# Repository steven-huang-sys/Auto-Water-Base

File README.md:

# Senior Design Project Fall 2024
## Autonomous Watering System - Base Station
This repository contains the code for the microcontroller used in the base station of the system. Not everything is uploaded as the repository would be way too big with the build files. I used the ESP-IDF setup within VSCode.

## Specifications
### Microcontrollers
Tested on an ESP-WROOM-32
Intended to be an ESP32-S3 on the final product

### Display
2.2in TFT LCD Display with ILI9488 Drivers. SPI interface

## Schematic Notes
This is on KiCAD 6.0. Footprints for the ESP32 can be found here: https://github.com/espressif/kicad-libraries/tree/legacy_kicad6?tab=readme-ov-file

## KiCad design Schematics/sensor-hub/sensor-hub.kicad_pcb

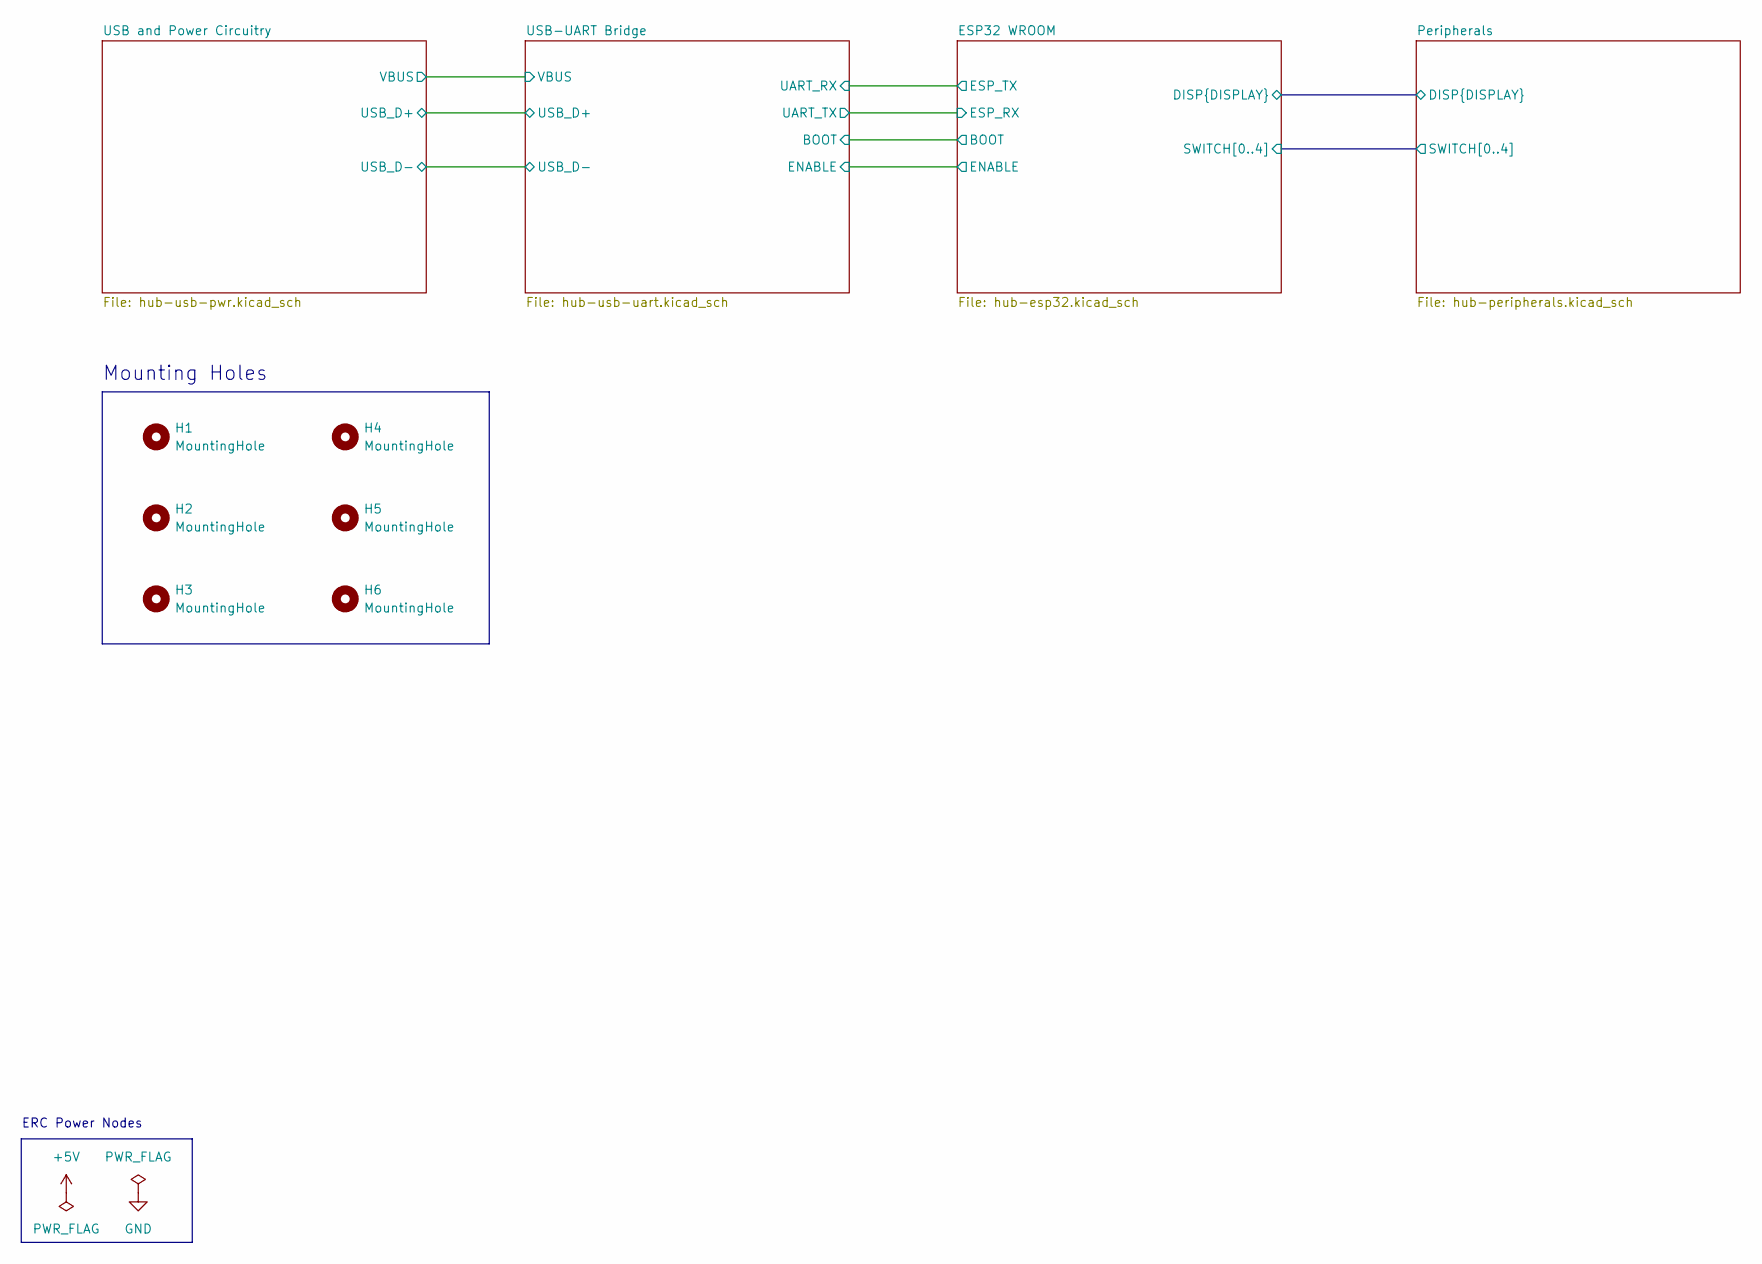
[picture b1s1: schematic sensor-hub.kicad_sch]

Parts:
H1, H2, H3, H4, H5, H6: MountingHole; MountingHole_3.2mm_M3

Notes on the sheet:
ERC Power Nodes
Mounting Holes

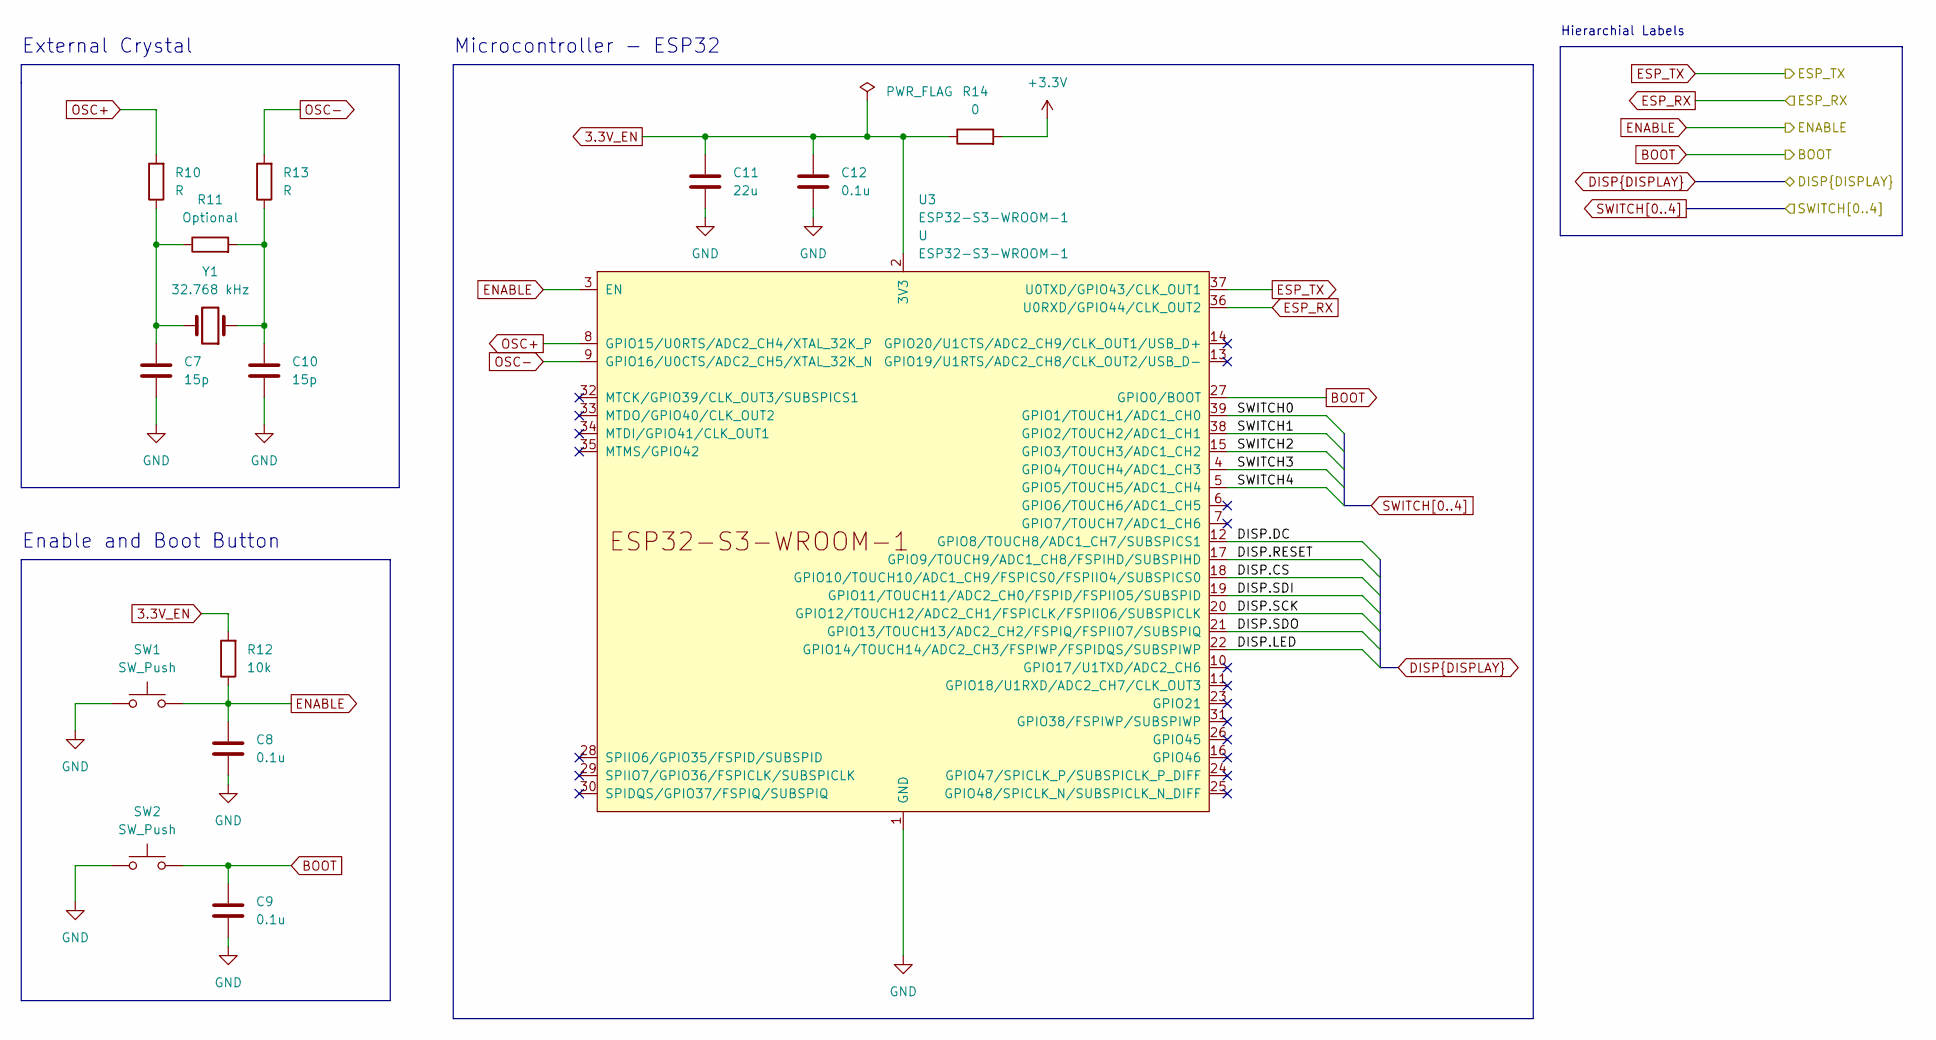
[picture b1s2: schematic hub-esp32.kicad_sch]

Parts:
C7, C10: 15p; C_0805_2012Metric_Pad1.18x1.45mm_HandSolder
C8, C9, C12: 0.1u; C_0805_2012Metric_Pad1.18x1.45mm_HandSolder
C11: 22u; C_0805_2012Metric_Pad1.18x1.45mm_HandSolder
R10, R13: R; R_0805_2012Metric_Pad1.20x1.40mm_HandSolder
R11: Optional; R_0805_2012Metric_Pad1.20x1.40mm_HandSolder
R12: 10k; R_0805_2012Metric_Pad1.20x1.40mm_HandSolder
R14: 0; R_0805_2012Metric_Pad1.20x1.40mm_HandSolder
SW1, SW2: SW_Push; Switch_Small
U3: ESP32-S3-WROOM-1; ESP32-S3-WROOM-1U
Y1: 32.768 kHz; Crystal_SMD_3215-2Pin_3.2x1.5mm

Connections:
3.3V_EN: C11.2, C12.2, R12.2, R14.1, U3.2 (3V3)
+3V3: R14.2; also elsewhere on the board
BOOT: C9.2, SW2.2, U3.27 (GPIO0/BOOT); also elsewhere on the board
DISP.CS: U3.18 (GPIO10/TOUCH10/ADC1_CH9/FSPICS0/FSPIIO4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); also elsewhere on the board
DISP.DC: U3.12 (GPIO8/TOUCH8/ADC1_CH7/SUBSPICS1); also elsewhere on the board
DISP.LED: U3.22 (GPIO14/TOUCH14/ADC2_CH3/FSPIWP/FSPIDQS/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); also elsewhere on the board
DISP.RESET: U3.17 (GPIO9/TOUCH9/ADC1_CH8/FSPIHD/SUBSPIHD); also elsewhere on the board
DISP.SCK: U3.20 (GPIO12/TOUCH12/ADC2_CH1/FSPICLK/FSPIIO6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); also elsewhere on the board
DISP.SDI: U3.19 (GPIO11/TOUCH11/ADC2_CH0/FSPID/FSPIIO5/S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); also elsewhere on the board
DISP.SDO: U3.21 (GPIO13/TOUCH13/ADC2_CH2/FSPIQ/FSPIIO7/S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); also elsewhere on the board
ENABLE: C8.2, R12.1, SW1.2, U3.3 (EN); also elsewhere on the board
ESP_RX: U3.36 (U0RXD/GPIO44/CLK_OUT2); also elsewhere on the board
GND: C7.2, C8.1, C9.1, C10.2, C11.1, C12.1, SW1.1, SW2.1, U3.1 (GND), U3.40 (GND), U3.41 (GND); also elsewhere on the board
unnamed: C7.1, R10.1, R11.1, Y1.2
unnamed: C10.1, R11.2, R13.1, Y1.1
OSC+: R10.2, U3.8 (GPIO15/U0RTS/ADC2_CH4/XTAL_32K_P)
OSC-: R13.2, U3.9 (GPIO16/U0CTS/ADC2_CH5/XTAL_32K_N)
SWITCH0: U3.39 (GPIO1/TOUCH1/ADC1_CH0); also elsewhere on the board
SWITCH1: U3.38 (GPIO2/TOUCH2/ADC1_CH1); also elsewhere on the board
SWITCH2: U3.15 (GPIO3/TOUCH3/ADC1_CH2); also elsewhere on the board
SWITCH3: U3.4 (GPIO4/TOUCH4/ADC1_CH3); also elsewhere on the board
SWITCH4: U3.5 (GPIO5/TOUCH5/ADC1_CH4); also elsewhere on the board
UART_RX: U3.37 (U0TXD/GPIO43/CLK_OUT1); also elsewhere on the board

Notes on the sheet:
External Crystal
Enable and Boot Button
Hierarchial Labels
Microcontroller - ESP32

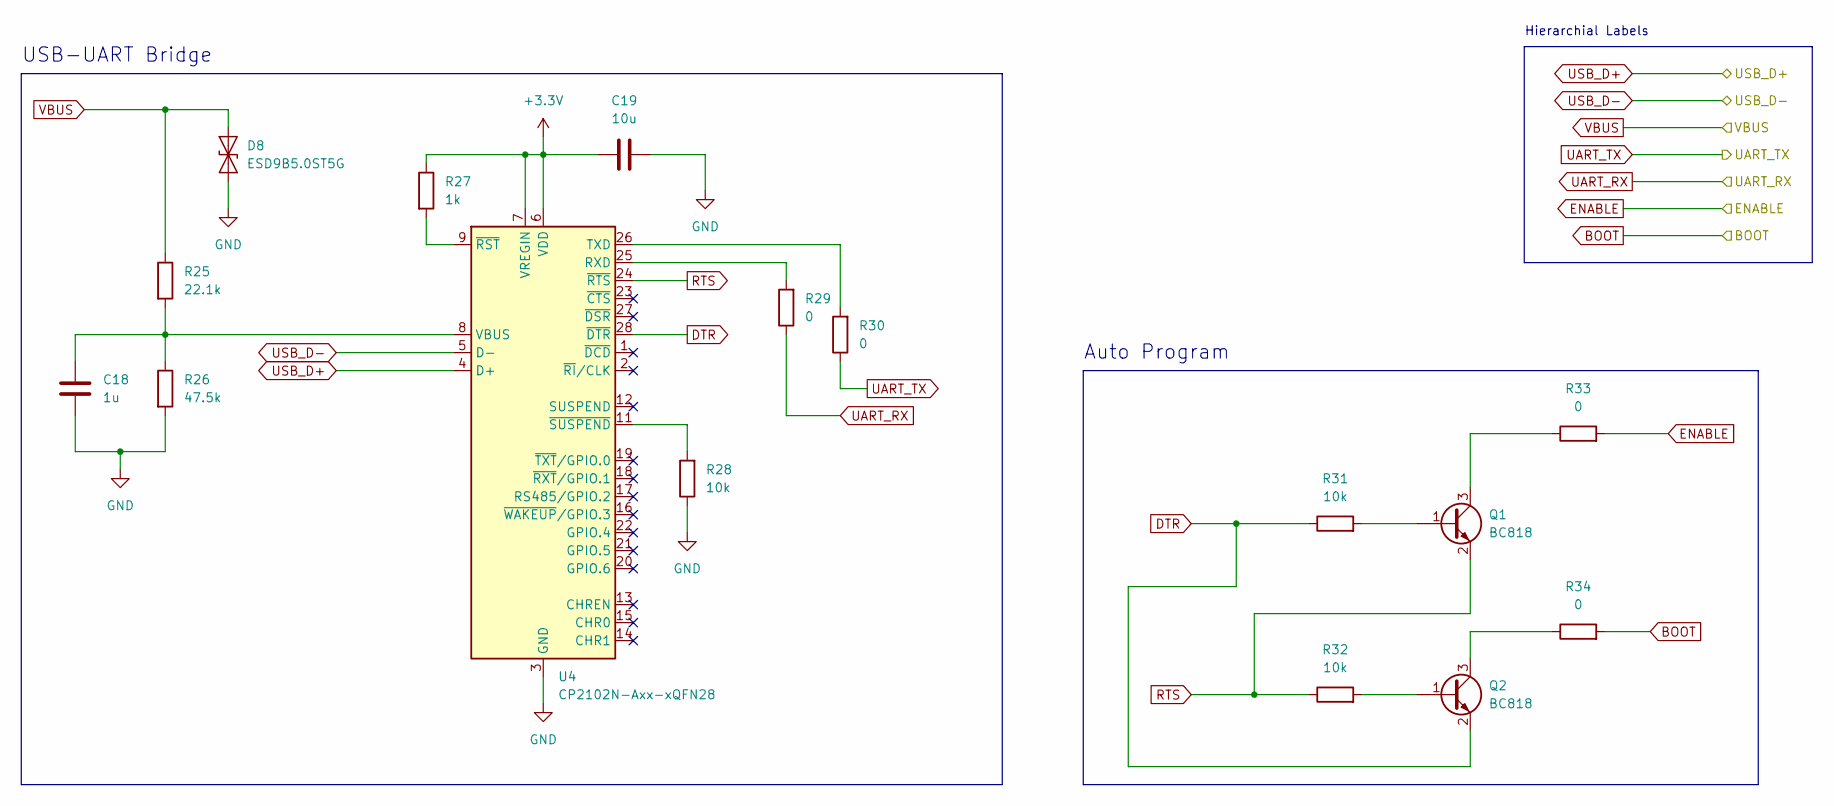
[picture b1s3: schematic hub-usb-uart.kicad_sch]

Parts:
C18: 1u; C_0805_2012Metric_Pad1.18x1.45mm_HandSolder
C19: 10u; C_0805_2012Metric_Pad1.18x1.45mm_HandSolder
D8: ESD9B5.0ST5G; D_SOD-923
Q1, Q2: BC818; SOT-23
R25: 22.1k; R_0805_2012Metric_Pad1.20x1.40mm_HandSolder
R26: 47.5k; R_0805_2012Metric_Pad1.20x1.40mm_HandSolder
R27: 1k; R_0805_2012Metric_Pad1.20x1.40mm_HandSolder
R28, R31, R32: 10k; R_0805_2012Metric_Pad1.20x1.40mm_HandSolder
R29, R30, R33, R34: 0; R_0805_2012Metric_Pad1.20x1.40mm_HandSolder
U4: CP2102N-Axx-xQFN28; QFN-28-1EP_5x5mm_P0.5mm_EP3.35x3.35mm

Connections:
+3V3: C19.1, R27.1, U4.6 (VDD), U4.7 (VREGIN); also elsewhere on the board
BOOT: R34.2; also elsewhere on the board
DTR: Q2.2 (E), R31.1, U4.28 (~DTR)
ENABLE: R33.2; also elsewhere on the board
ESP_RX: R30.1; also elsewhere on the board
GND: C18.1, C19.2, D8.2 (A2), R26.2, R28.1, U4.3 (GND), U4.29 (GND); also elsewhere on the board
unnamed: C18.2, R25.2, R26.1, U4.8 (VBUS)
unnamed: Q1.1 (B), R31.2
unnamed: Q1.3 (C), R33.1
unnamed: Q2.1 (B), R32.2
unnamed: Q2.3 (C), R34.1
unnamed: R27.2, U4.9 (~RST)
unnamed: R28.2, U4.11 (~SUSPEND)
unnamed: R29.2, U4.25 (RXD)
unnamed: R30.2, U4.26 (TXD)
RTS: Q1.2 (E), R32.1, U4.24 (~RTS)
UART_RX: R29.1; also elsewhere on the board
USB_D+: U4.4 (D+); also elsewhere on the board
USB_D-: U4.5 (D-); also elsewhere on the board
VBUS: D8.1 (A1), R25.1; also elsewhere on the board

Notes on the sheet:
Auto Program
Hierarchial Labels
USB-UART Bridge

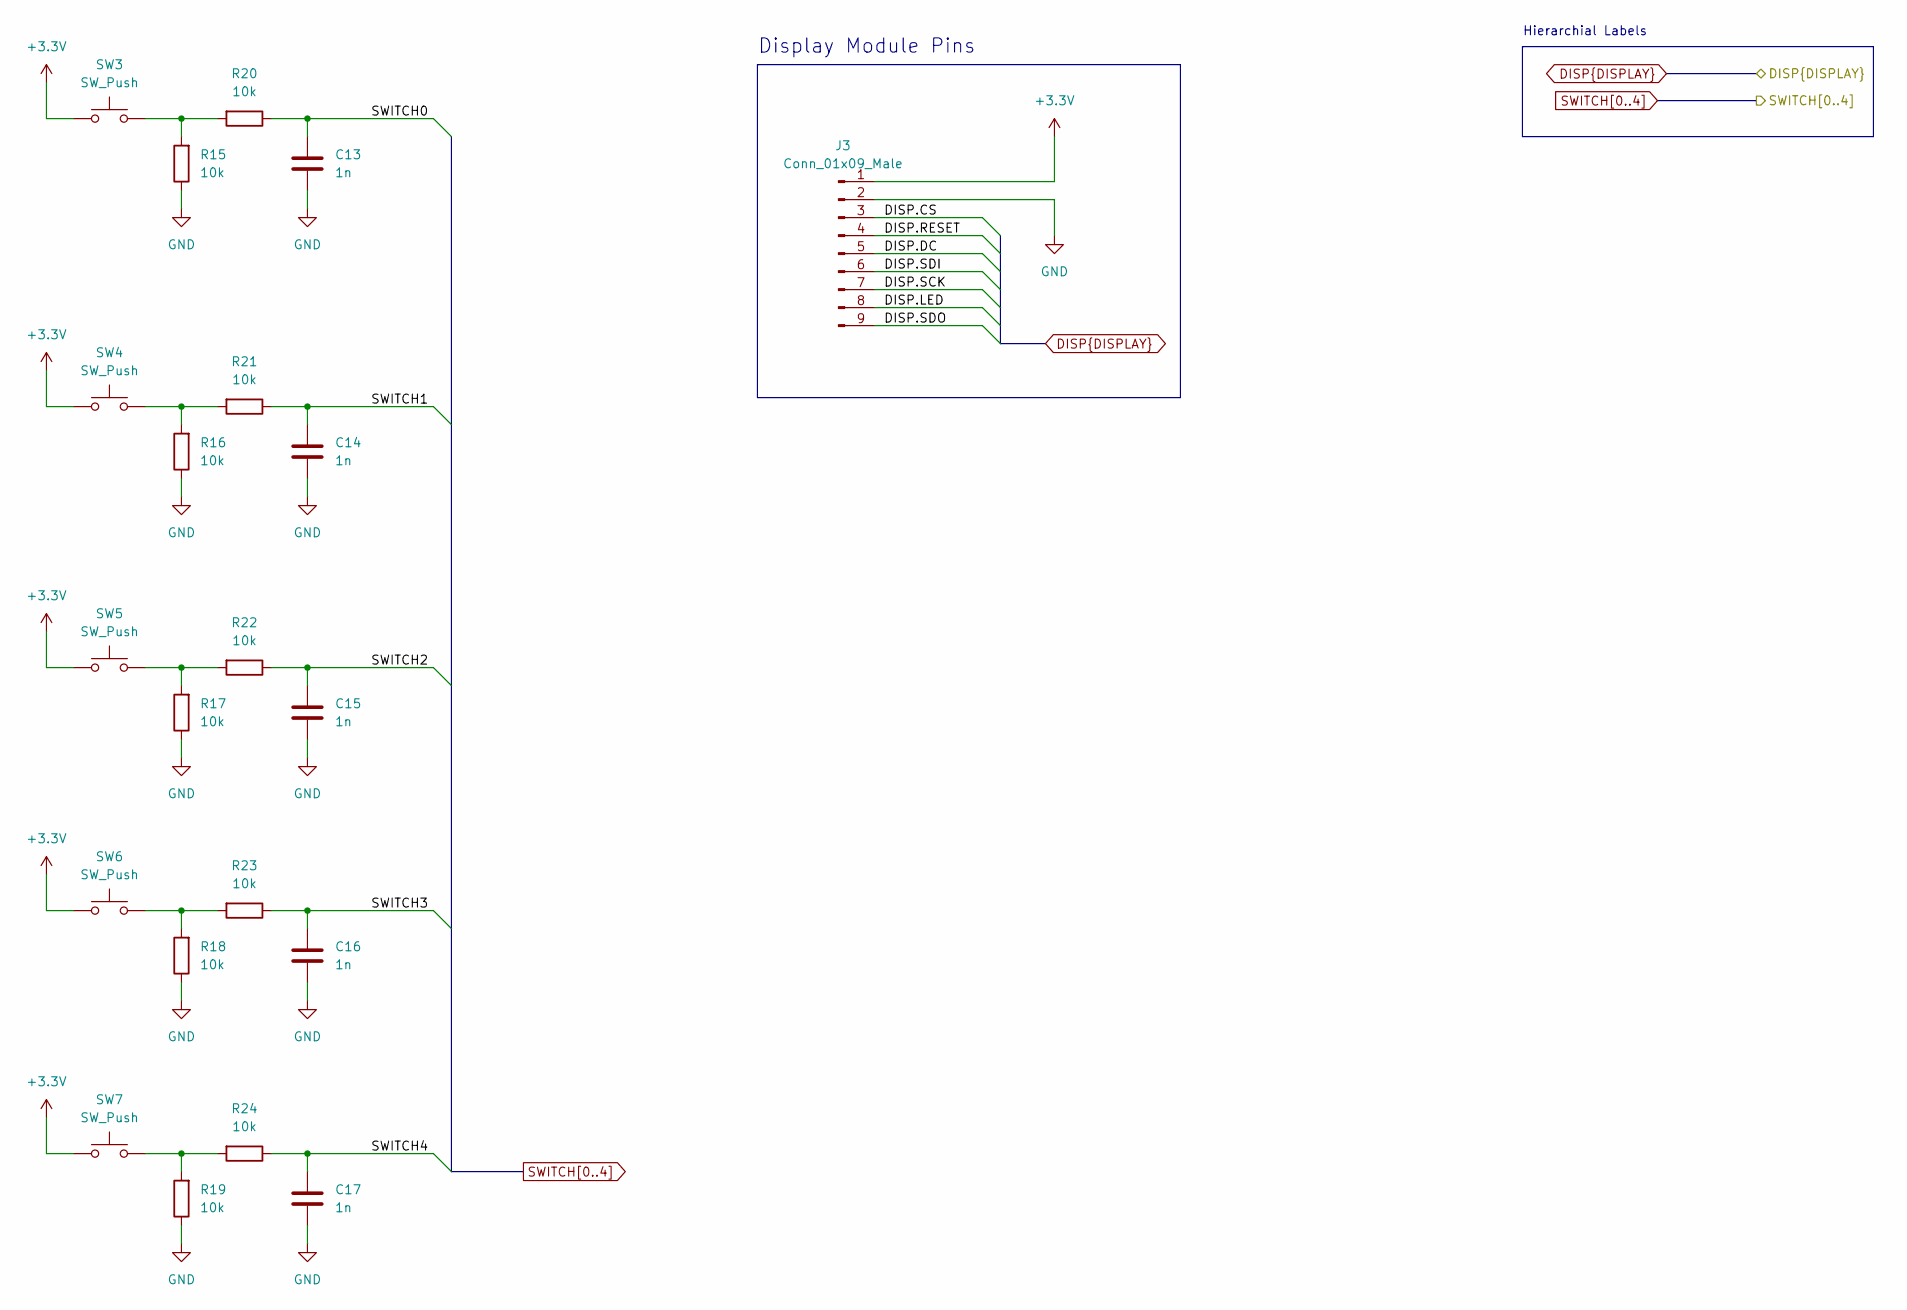
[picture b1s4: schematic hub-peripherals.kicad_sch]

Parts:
C13, C14, C15, C16, C17: 1n; C_0805_2012Metric_Pad1.18x1.45mm_HandSolder
J3: Conn_01x09_Male; PinHeader_1x09_P2.54mm_Vertical
R15, R16, R17, R18, R19, R20, R21, R22, R23, R24: 10k; R_0805_2012Metric_Pad1.20x1.40mm_HandSolder
SW3, SW4, SW5, SW6, SW7: SW_Push; SW_PUSH-12mm

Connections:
+3V3: J3.1, SW3.1, SW4.1, SW5.1, SW6.1, SW7.1; also elsewhere on the board
DISP.CS: J3.3; also elsewhere on the board
DISP.DC: J3.5; also elsewhere on the board
DISP.LED: J3.8; also elsewhere on the board
DISP.RESET: J3.4; also elsewhere on the board
DISP.SCK: J3.7; also elsewhere on the board
DISP.SDI: J3.6; also elsewhere on the board
DISP.SDO: J3.9; also elsewhere on the board
GND: C13.1, C14.1, C15.1, C16.1, C17.1, J3.2, R15.1, R16.1, R17.1, R18.1, R19.1; also elsewhere on the board
unnamed: R15.2, R20.2, SW3.2
unnamed: R16.2, R21.2, SW4.2
unnamed: R17.2, R22.2, SW5.2
unnamed: R18.2, R23.2, SW6.2
unnamed: R19.2, R24.2, SW7.2
SWITCH0: C13.2, R20.1; also elsewhere on the board
SWITCH1: C14.2, R21.1; also elsewhere on the board
SWITCH2: C15.2, R22.1; also elsewhere on the board
SWITCH3: C16.2, R23.1; also elsewhere on the board
SWITCH4: C17.2, R24.1; also elsewhere on the board

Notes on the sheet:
Display Module Pins
Hierarchial Labels

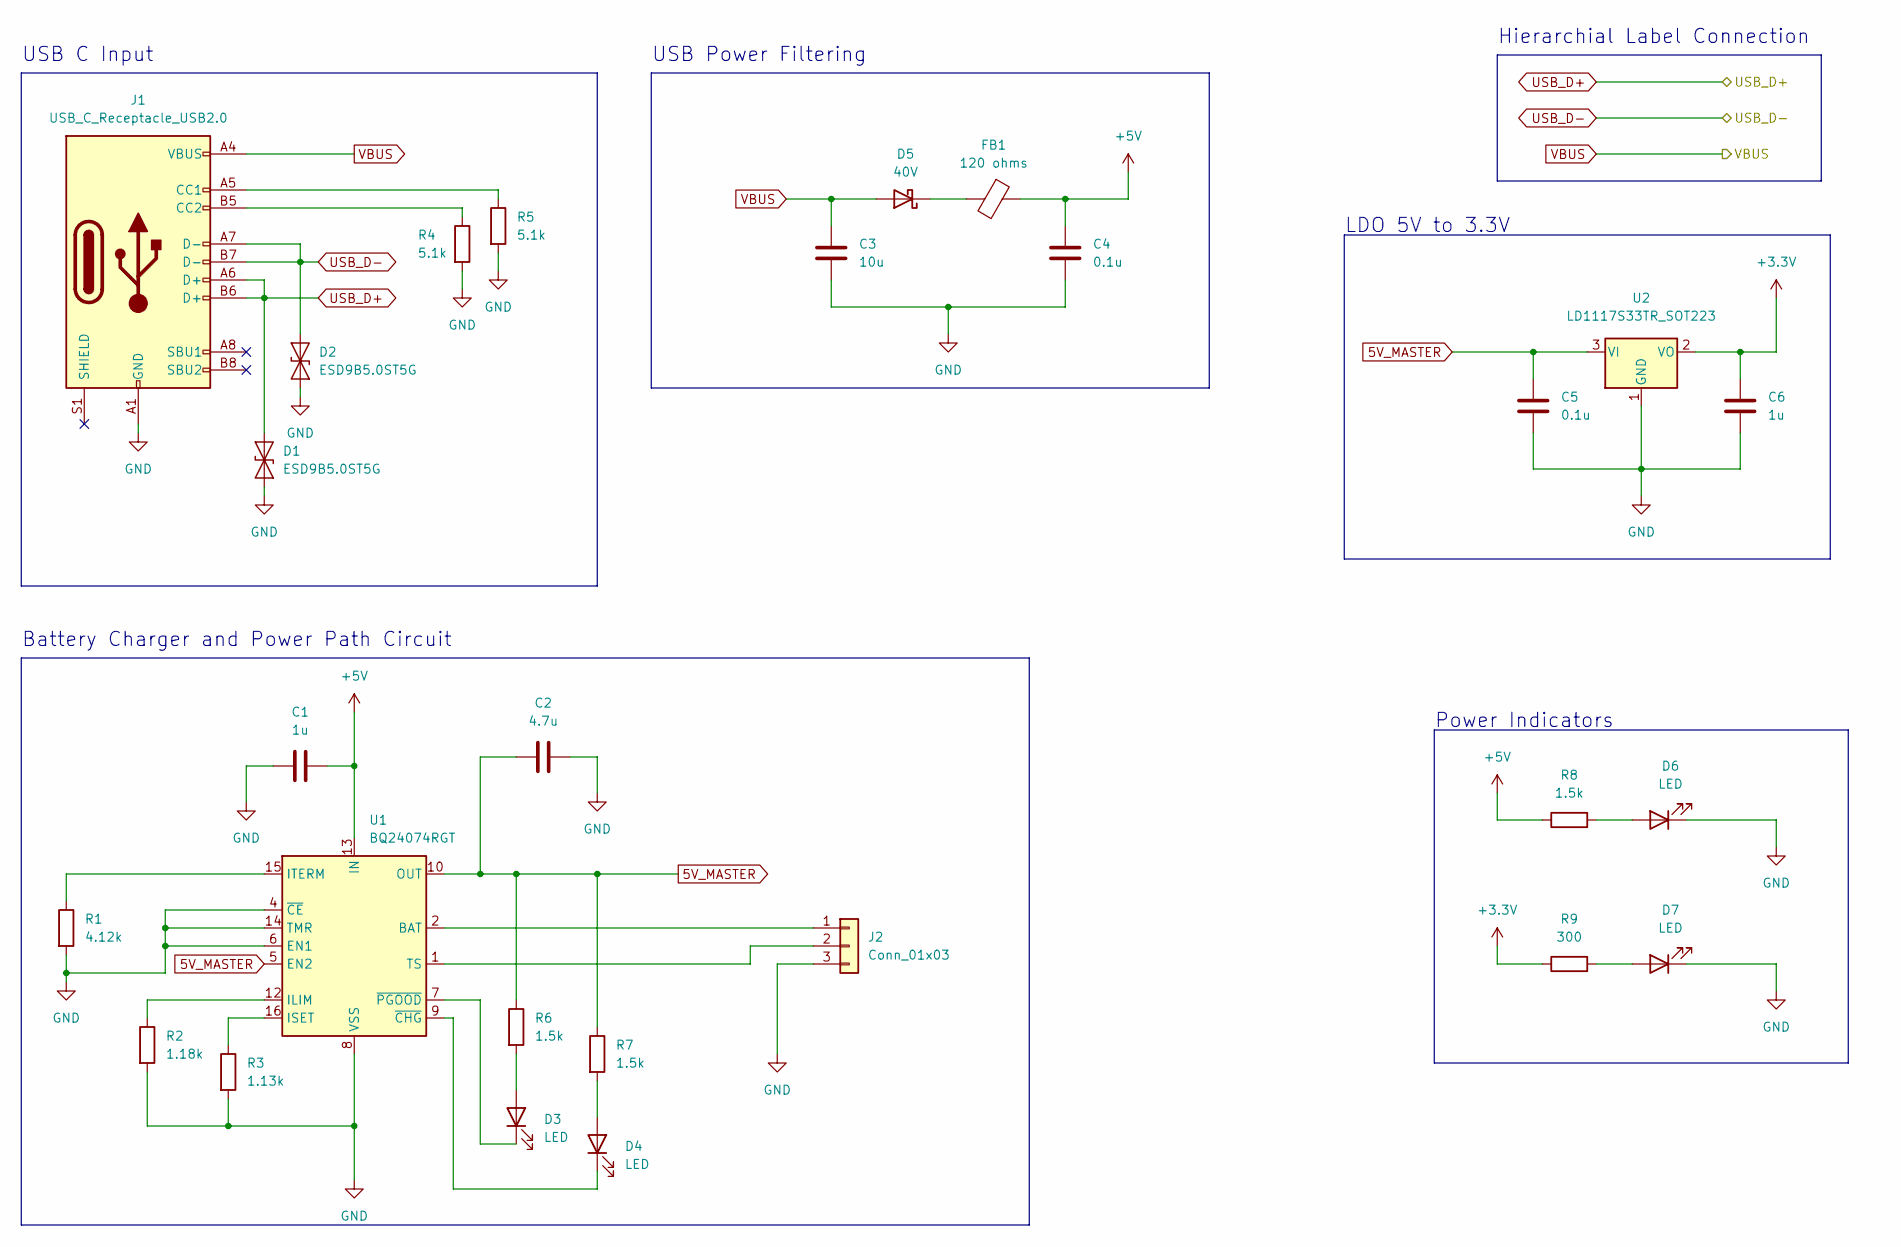
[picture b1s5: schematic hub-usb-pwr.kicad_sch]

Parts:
C1, C6: 1u; C_0805_2012Metric_Pad1.18x1.45mm_HandSolder
C2: 4.7u; C_0805_2012Metric_Pad1.18x1.45mm_HandSolder
C3: 10u; C_0805_2012Metric_Pad1.18x1.45mm_HandSolder
C4, C5: 0.1u; C_0805_2012Metric_Pad1.18x1.45mm_HandSolder
D1, D2: ESD9B5.0ST5G; D_SOD-923
D3, D4, D6, D7: LED; LED_0805_2012Metric_Pad1.15x1.40mm_HandSolder
D5: 40V; D_SOD-123F
FB1: 120 ohms; R_0805_2012Metric_Pad1.20x1.40mm_HandSolder
J1: USB_C_Receptacle_USB2.0; USB_C_Receptacle_HRO_TYPE-C-31-M-12
J2: Conn_01x03; JST_PH_B3B-PH-K_1x03_P2.00mm_Vertical
R1: 4.12k; R_0805_2012Metric_Pad1.20x1.40mm_HandSolder
R2: 1.18k; R_0805_2012Metric_Pad1.20x1.40mm_HandSolder
R3: 1.13k; R_0805_2012Metric_Pad1.20x1.40mm_HandSolder
R4, R5: 5.1k; R_0805_2012Metric_Pad1.20x1.40mm_HandSolder
R6, R7, R8: 1.5k; R_0805_2012Metric_Pad1.20x1.40mm_HandSolder
R9: 300; R_0805_2012Metric_Pad1.20x1.40mm_HandSolder
U1: BQ24074RGT; VQFN-16-1EP_3x3mm_P0.5mm_EP1.6x1.6mm
U2: LD1117S33TR_SOT223; SOT-223-3_TabPin2

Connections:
5V_MASTER: C2.1, C5.1, R6.1, R7.1, U1.5 (EN2), U1.10 (OUT), U1.11 (OUT), U2.3 (VI)
+3V3: C6.2, R9.1, U2.2 (VO); also elsewhere on the board
+5V: C1.2, C4.1, FB1.1, R8.1, U1.13 (IN)
GND: C1.1, C2.2, C3.2, C4.2, C5.2, C6.1, D1.2 (A2), D2.2 (A2), D6.1 (K), D7.1 (K), J1.A1 (GND), J1.A12 (GND), J1.B1 (GND), J1.B12 (GND), J2.3, R1.2, R2.2, R3.2, R4.2, R5.2, U1.4 (~CE), U1.6 (EN1), U1.8 (VSS), U1.14 (TMR), U1.17 (VSS), U2.1 (GND); also elsewhere on the board
unnamed: D3.1 (K), U1.7 (~PGOOD)
unnamed: D3.2 (A), R6.2
unnamed: D4.1 (K), U1.9 (~CHG)
unnamed: D4.2 (A), R7.2
unnamed: D5.1 (K), FB1.2
unnamed: D6.2 (A), R8.2
unnamed: D7.2 (A), R9.2
unnamed: J1.A5 (CC1), R5.1
unnamed: J1.B5 (CC2), R4.1
unnamed: J2.1, U1.2 (BAT), U1.3 (BAT)
unnamed: J2.2, U1.1 (TS)
unnamed: R1.1, U1.15 (ITERM)
unnamed: R2.1, U1.12 (ILIM)
unnamed: R3.1, U1.16 (ISET)
USB_D+: D1.1 (A1), J1.A6 (D+), J1.B6 (D+); also elsewhere on the board
USB_D-: D2.1 (A1), J1.A7 (D-), J1.B7 (D-); also elsewhere on the board
VBUS: C3.1, D5.2 (A), J1.A4 (VBUS), J1.A9 (VBUS), J1.B4 (VBUS), J1.B9 (VBUS); also elsewhere on the board

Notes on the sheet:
Hierarchial Label Connection
LDO 5V to 3.3V
Power Indicators
USB Power Filtering
USB C Input
Battery Charger and Power Path Circuit

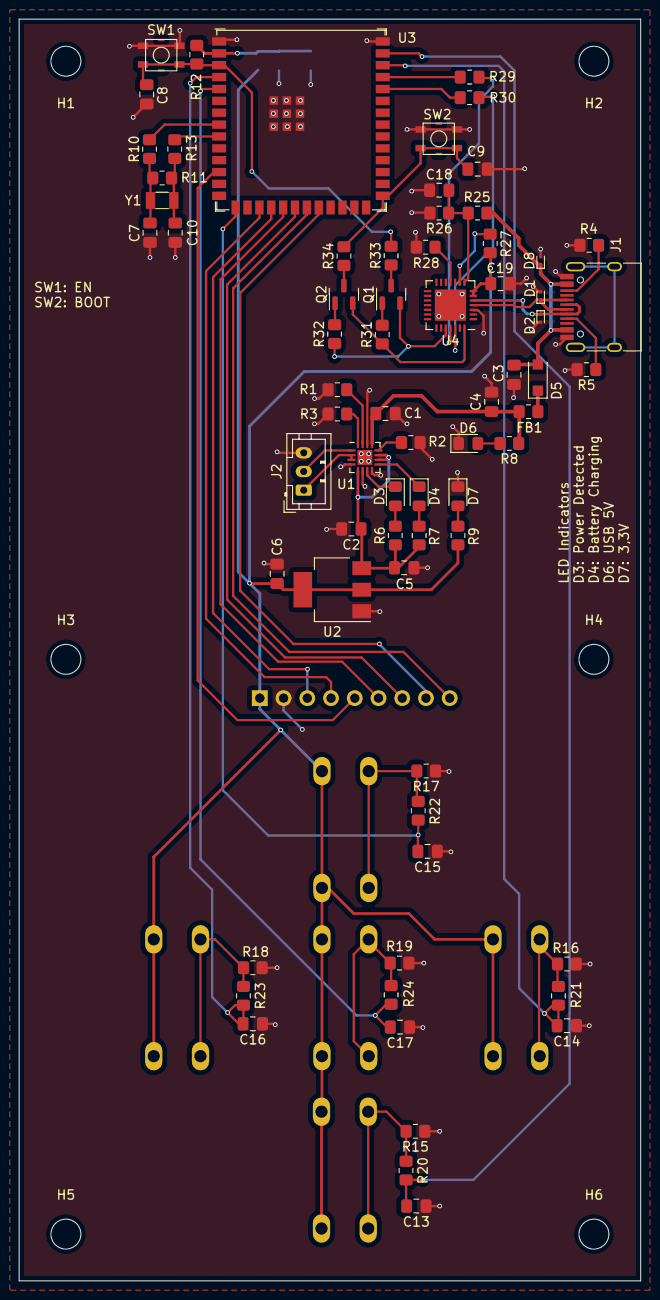
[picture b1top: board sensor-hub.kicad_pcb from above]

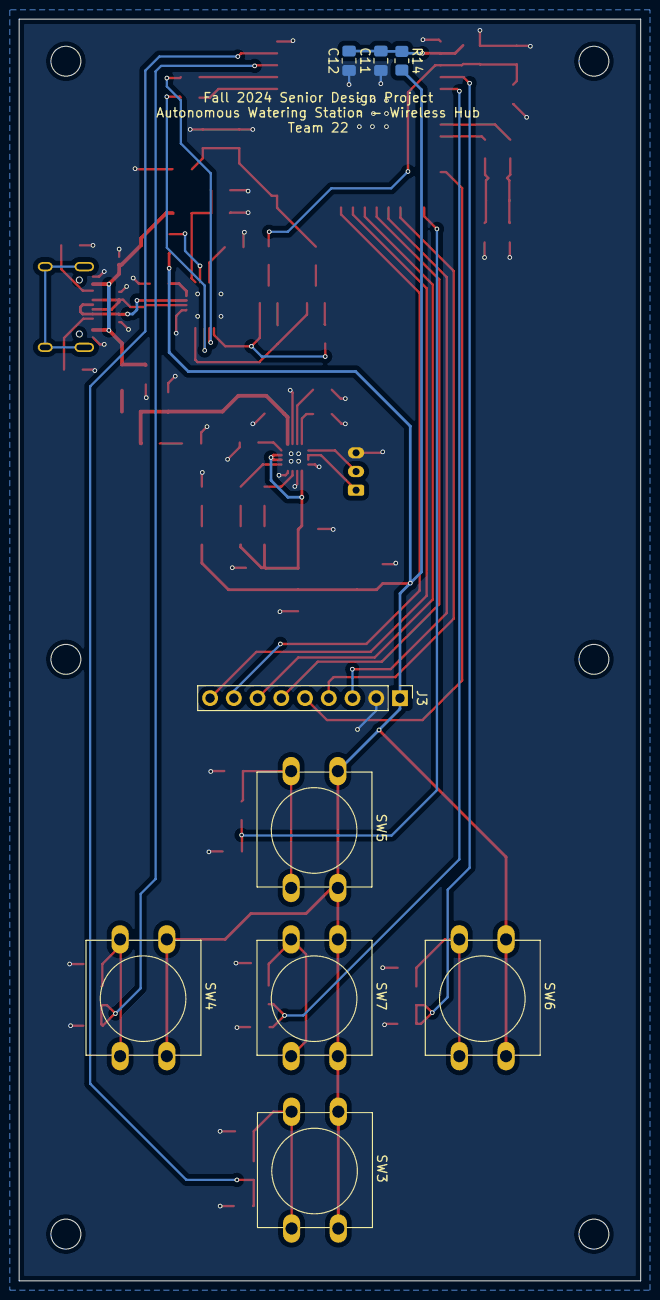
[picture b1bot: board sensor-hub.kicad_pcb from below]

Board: 2 copper layers, 66.5 x 135.0 mm, 85 parts (9 on the bottom side), 58 nets.

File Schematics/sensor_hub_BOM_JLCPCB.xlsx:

Comment | Designator | Footprint | JLCPCB Part#(optional)
1u | C1, C6, C18 | Capacitor_SMD:C_0805_2012Metric_Pad1.18x1.45mm_HandSolder | C116352
4.7u | C2 | Capacitor_SMD:C_0805_2012Metric_Pad1.18x1.45mm_HandSolder | C1779
10u | C3, C19 | Capacitor_SMD:C_0805_2012Metric_Pad1.18x1.45mm_HandSolder | C15850
0.1u | C4, C5, C8, C9, C12 | Capacitor_SMD:C_0805_2012Metric_Pad1.18x1.45mm_HandSolder | C1711
15p | C7, C10 | Capacitor_SMD:C_0805_2012Metric_Pad1.18x1.45mm_HandSolder | C63339
22u | C11 | Capacitor_SMD:C_0805_2012Metric_Pad1.18x1.45mm_HandSolder | C45783
1n | C13, C14, C15, C16, C17 | Capacitor_SMD:C_0805_2012Metric_Pad1.18x1.45mm_HandSolder | C46653
ESD9B5.0ST5G | D1, D2, D8 | Diode_SMD:D_SOD-923 | C111566
LED | D3, D4, D6, D7 | LED_SMD:LED_0805_2012Metric_Pad1.15x1.40mm_HandSolder | C2297
40V | D5 | Diode_SMD:D_SOD-123F | C779674
120 ohms | FB1 | Resistor_SMD:R_0805_2012Metric_Pad1.20x1.40mm_HandSolder | C79382
MountingHole | H1, H2, H3, H4, H5, H6 | MountingHole:MountingHole_3.2mm_M3
USB_C_Receptacle_USB2.0 | J1 | Connector_USB:USB_C_Receptacle_HRO_TYPE-C-31-M-12 | C165948
Conn_01x03 | J2 | Connector_JST:JST_PH_B3B-PH-K_1x03_P2.00mm_Vertical | C131339
Conn_01x09_Male | J3 | Connector_PinHeader_2.54mm:PinHeader_1x09_P2.54mm_Vertical | C22438292
BC818 | Q1, Q2 | Package_TO_SOT_SMD:SOT-23 | C154797
4.12k | R1 | Resistor_SMD:R_0805_2012Metric_Pad1.20x1.40mm_HandSolder | C218607
1.18k | R2 | Resistor_SMD:R_0805_2012Metric_Pad1.20x1.40mm_HandSolder | C2077400
1.13k | R3 | Resistor_SMD:R_0805_2012Metric_Pad1.20x1.40mm_HandSolder | C322246
5.1k | R4, R5 | Resistor_SMD:R_0805_2012Metric_Pad1.20x1.40mm_HandSolder | C26023
1.5k | R6, R7, R8 | Resistor_SMD:R_0805_2012Metric_Pad1.20x1.40mm_HandSolder | C126687
300 | R9 | Resistor_SMD:R_0805_2012Metric_Pad1.20x1.40mm_HandSolder | C2828726
R | R10, R13 | Resistor_SMD:R_0805_2012Metric_Pad1.20x1.40mm_HandSolder | C25275
Optional | R11 | Resistor_SMD:R_0805_2012Metric_Pad1.20x1.40mm_HandSolder
10k | R12, R15, R16, R17, R18, R19, R20, R21, R22, R23, R24, R28, R31, R32 | Resistor_SMD:R_0805_2012Metric_Pad1.20x1.40mm_HandSolder | C17414
0 | R14, R29, R30, R33, R34 | Resistor_SMD:R_0805_2012Metric_Pad1.20x1.40mm_HandSolder | C25275
22.1k | R25 | Resistor_SMD:R_0805_2012Metric_Pad1.20x1.40mm_HandSolder | C17552
47.5k | R26 | Resistor_SMD:R_0805_2012Metric_Pad1.20x1.40mm_HandSolder | C26011
1k | R27 | Resistor_SMD:R_0805_2012Metric_Pad1.20x1.40mm_HandSolder | C25623
SW_Push | SW1, SW2 | JLCPCB_Components:Switch_Small | C967766
SW_Push | SW3, SW4, SW5, SW6, SW7 | Button_Switch_THT:SW_PUSH-12mm
BQ24074RGT | U1 | Package_DFN_QFN:VQFN-16-1EP_3x3mm_P0.5mm_EP1.6x1.6mm | C54313
LD1117S33TR_SOT223 | U2 | Package_TO_SOT_SMD:SOT-223-3_TabPin2 | C86781
ESP32-S3-WROOM-1 | U3 | Espressif:ESP32-S3-WROOM-1U | C3013946
CP2102N-Axx-xQFN28 | U4 | Package_DFN_QFN:QFN-28-1EP_5x5mm_P0.5mm_EP3.35x3.35mm | C964632
32.768 kHz | Y1 | Crystal:Crystal_SMD_3215-2Pin_3.2x1.5mm

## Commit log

2024-09-19 all test programs
2024-09-19 initial schematic files
2024-09-20 main board setup
2024-09-26 managers meeting schematics
2024-09-26 components library
2024-10-01 wifi + ble enabled simultaneously
2024-10-03 all 3 might be working
2024-11-07 schematic and pcb upload
2024-11-07 removing ESP32 test and small updates
2024-11-08 updated BOM and pick and place
2024-11-08 drill files added
2024-11-08 evenly spaced out switches
2024-12-03 this does not work
2024-12-05 pre SPARK challenge upload, no display or schedule
